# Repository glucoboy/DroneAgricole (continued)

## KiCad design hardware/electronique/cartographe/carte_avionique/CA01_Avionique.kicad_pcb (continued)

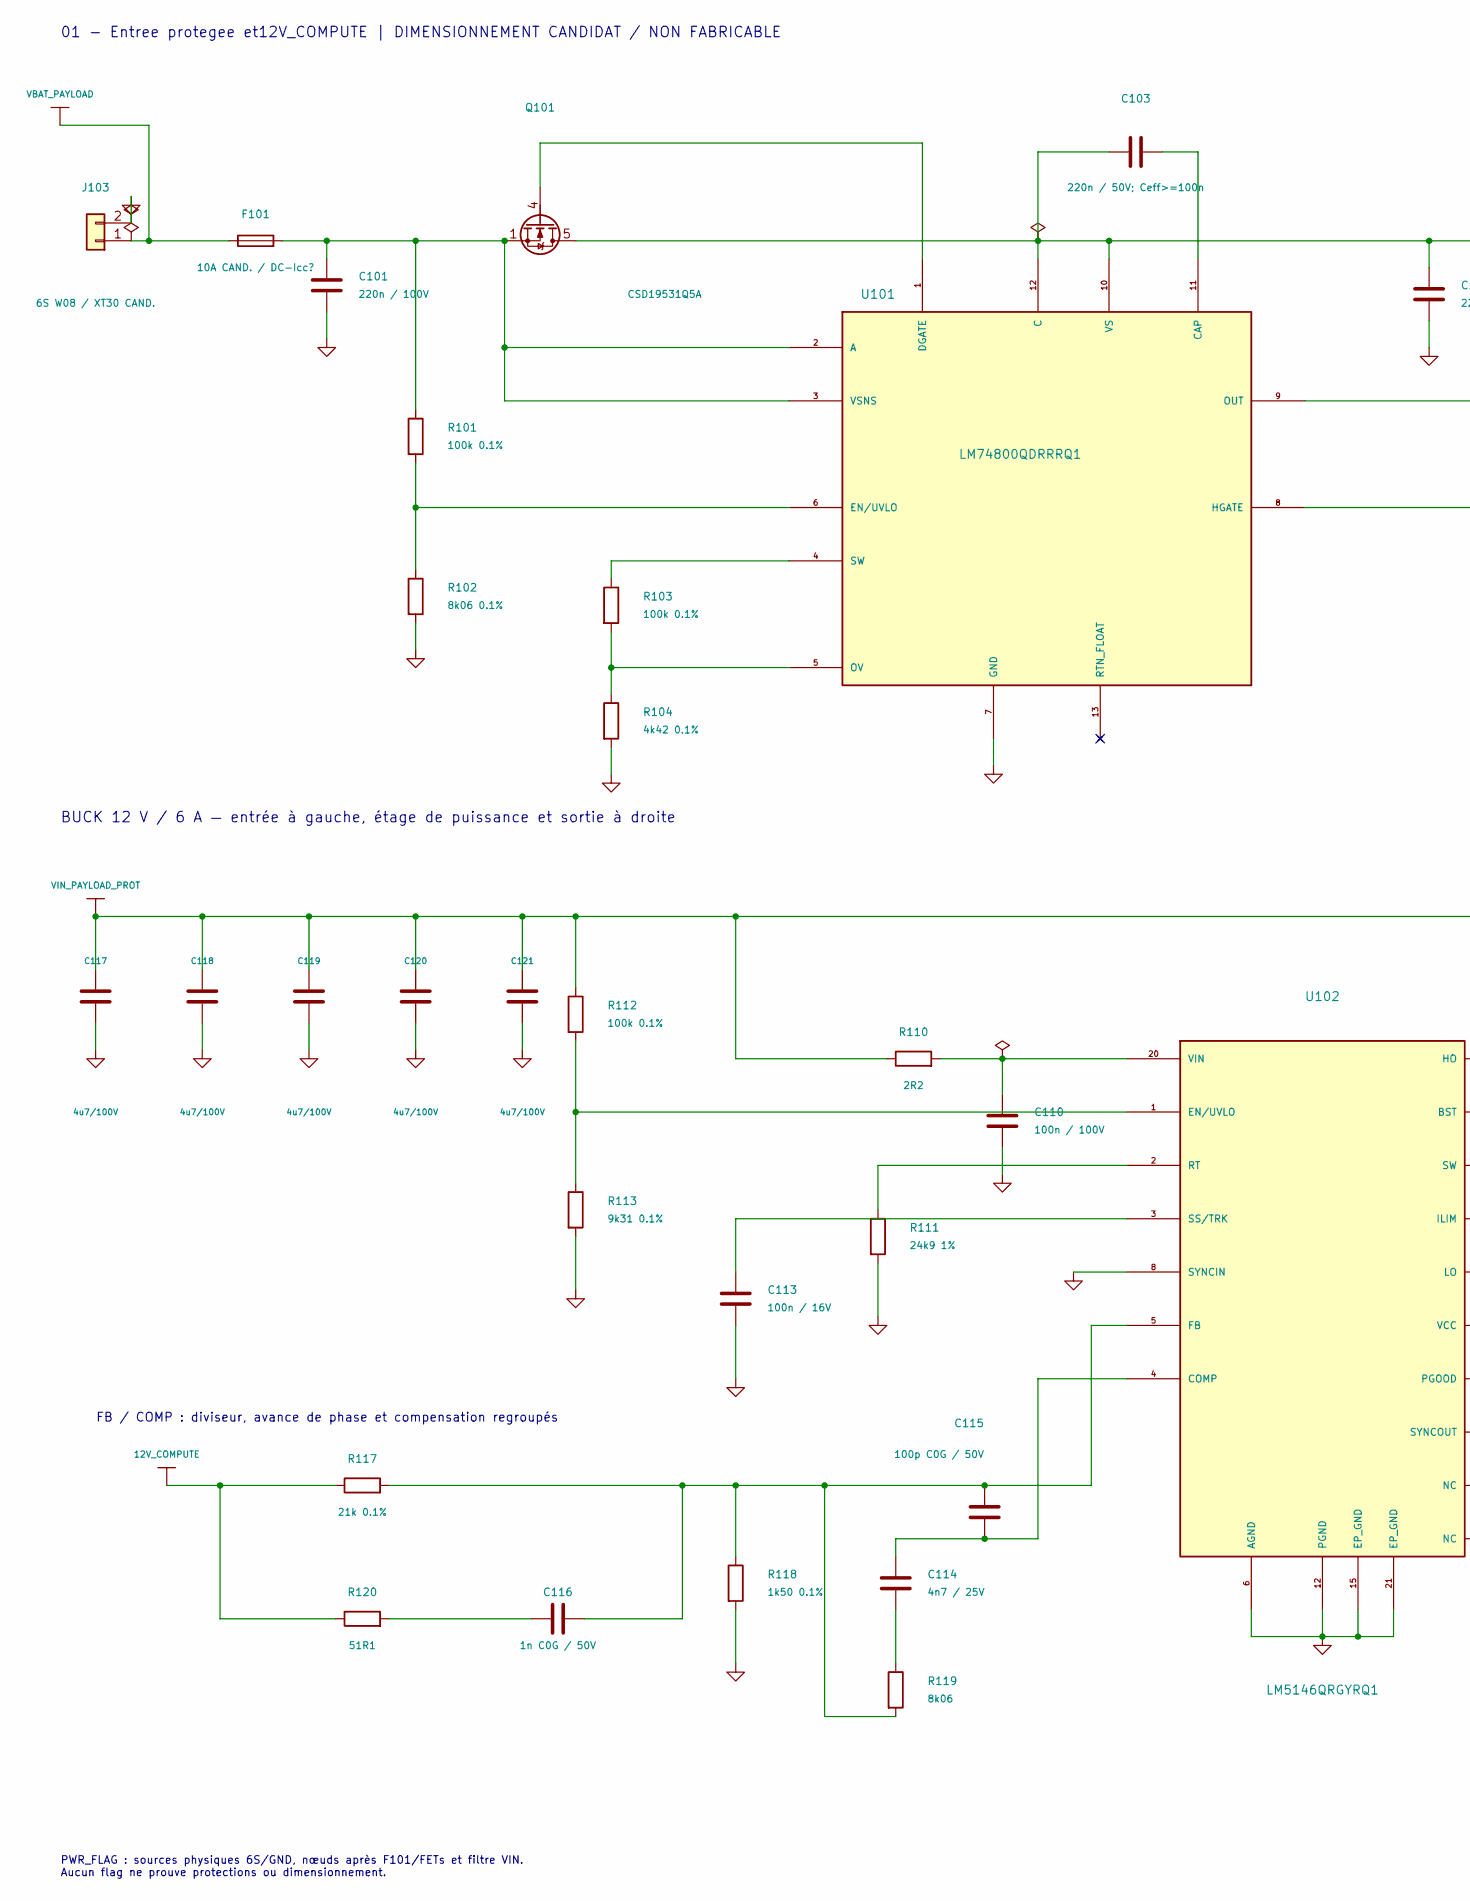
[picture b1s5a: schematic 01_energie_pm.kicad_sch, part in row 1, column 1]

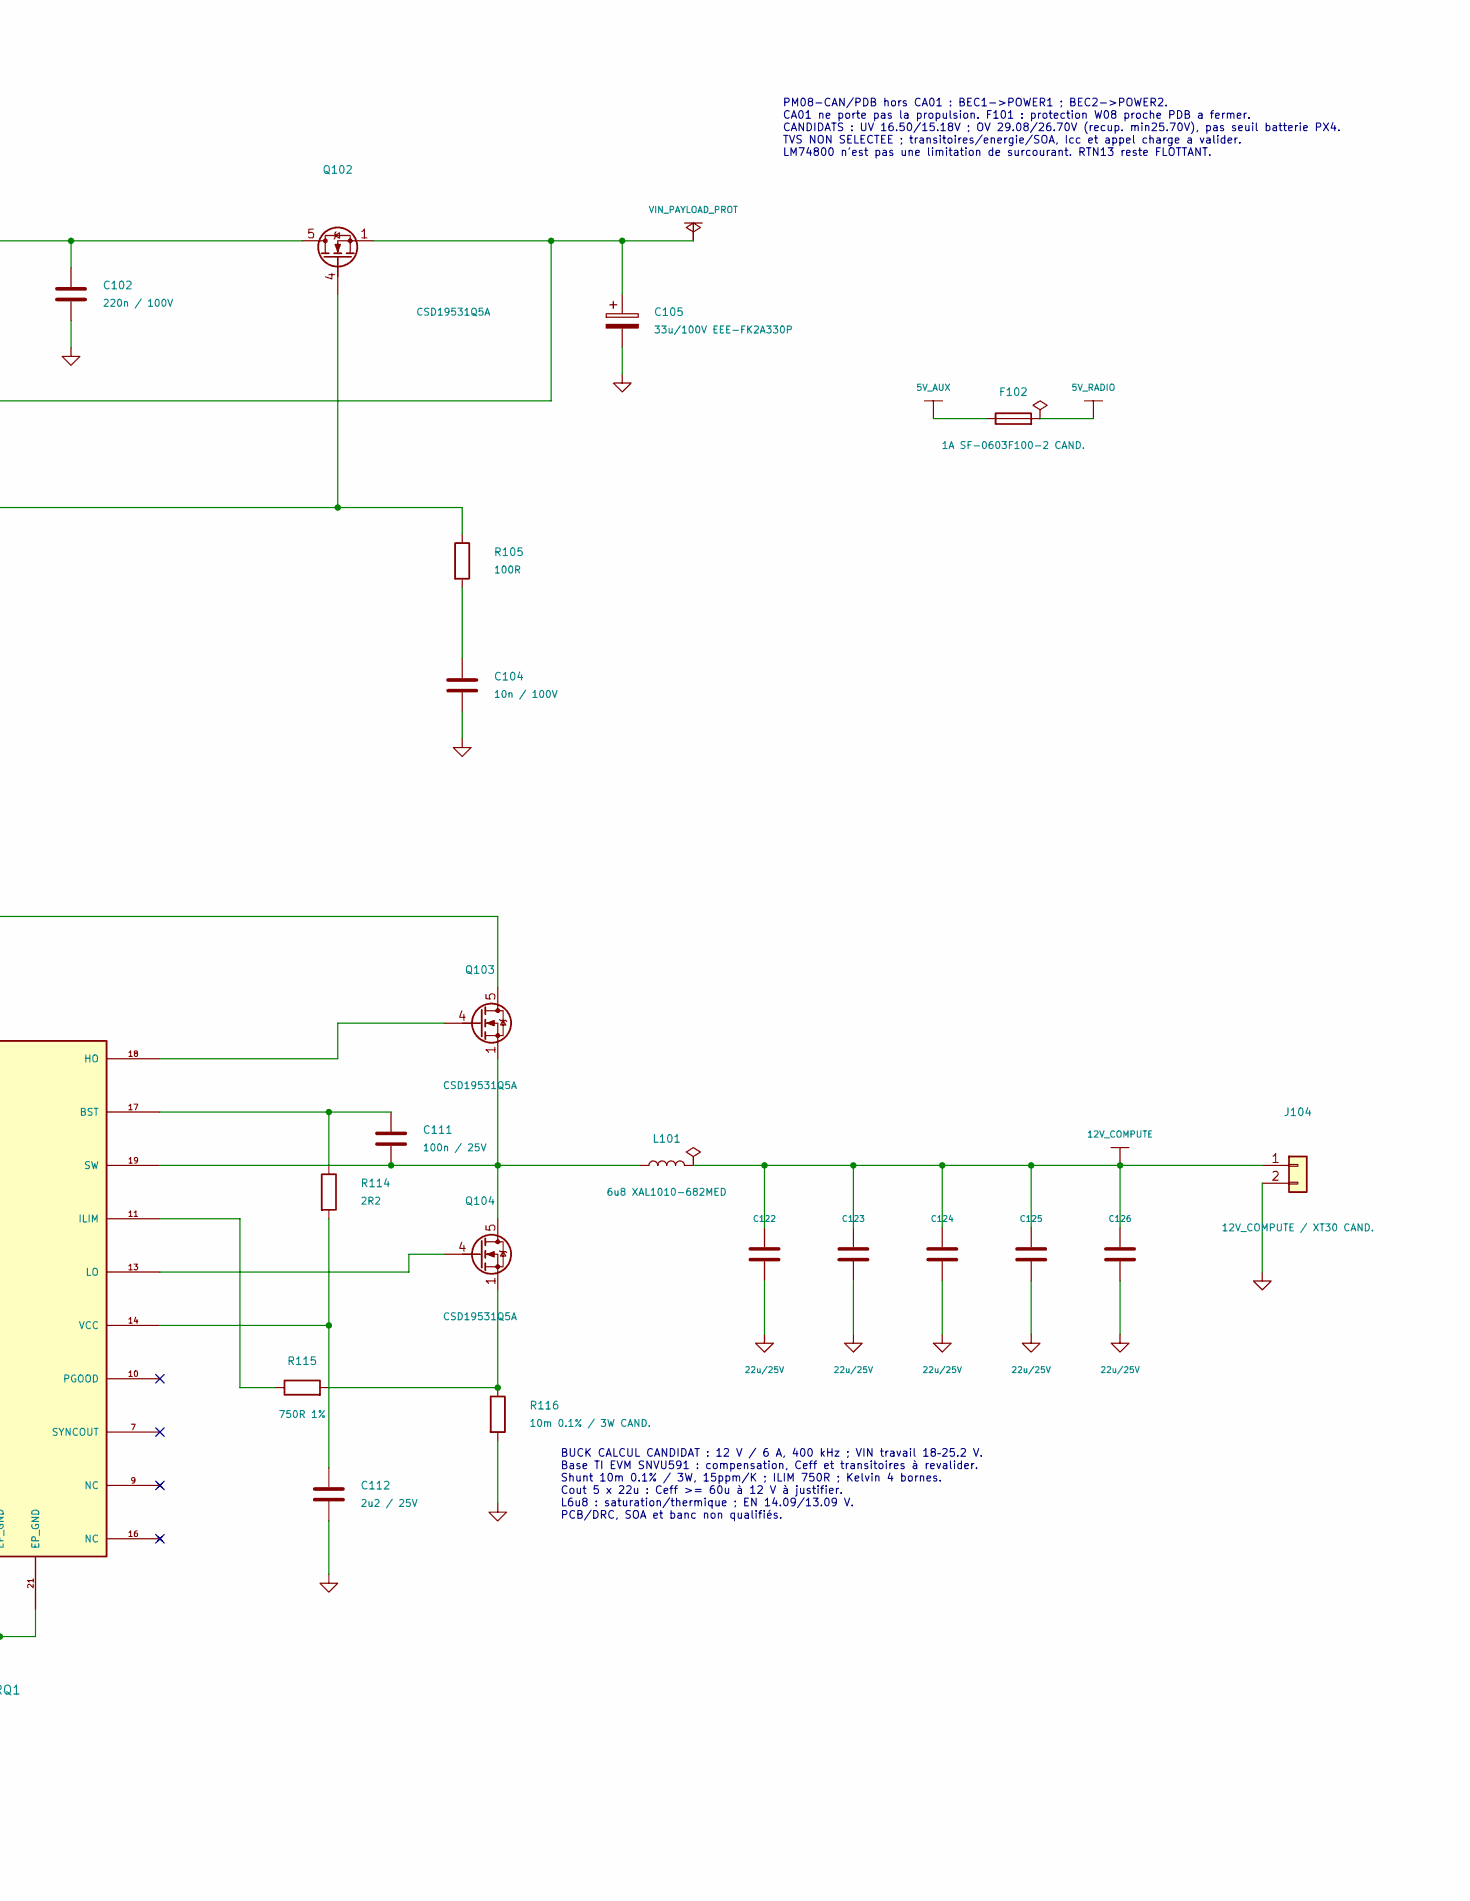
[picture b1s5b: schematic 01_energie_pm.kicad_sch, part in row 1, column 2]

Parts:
C101, C102: 220n / 100V; C_0603_1608Metric
C103: 220n / 50V; Ceff>=100n; C_0603_1608Metric
C104: 10n / 100V; C_0603_1608Metric
C105: 33u/100V EEE-FK2A330P; CP_Elec_8x10.5; MPN EEE-FK2A330P
C110: 100n / 100V; C_0603_1608Metric
C111: 100n / 25V; C_0603_1608Metric
C112: 2u2 / 25V; C_0603_1608Metric
C113: 100n / 16V; C_0603_1608Metric
C114: 4n7 / 25V; C_0603_1608Metric
C115: 100p C0G / 50V; C_0603_1608Metric
C116: 1n C0G / 50V; C_0603_1608Metric
C117, C118, C119, C120, C121: 4u7/100V; C_1210_3225Metric
C122, C123, C124, C125, C126: 22u/25V; C_1210_3225Metric
F101: 10A CAND. / DC-Icc?; Fuse_Littelfuse-NANO2-451_453; MPN 0451010.MRL
F102: 1A SF-0603F100-2 CAND.; Fuse_0603_1608Metric; MPN SF-0603F100-2
J103: 6S W08 / XT30 CAND.; XT30PW_M_CA01_PositivePin1; MPN XT30PW-M30.G.Y
J104: 12V_COMPUTE / XT30 CAND.; XT30PW_F_CA01_PositivePin1; MPN XT30PW-F30.G.Y
L101: 6u8 XAL1010-682MED; L_Coilcraft_XAL1010-XXX; MPN XAL1010-682MED
Q101, Q102, Q103, Q104: CSD19531Q5A; TI_Q5A_CSD19531; MPN CSD19531Q5A
R101, R103, R112: 100k 0.1%; R_0603_1608Metric
R102: 8k06 0.1%; R_0603_1608Metric
R104: 4k42 0.1%; R_0603_1608Metric
R105: 100R; R_0603_1608Metric
R110, R114: 2R2; R_0603_1608Metric
R111: 24k9 1%; R_0603_1608Metric
R113: 9k31 0.1%; R_0603_1608Metric
R115: 750R 1%; R_0603_1608Metric
R116: 10m 0.1% / 3W CAND.; VPG_CSM3637; MPN Y14880R01000B9R
R117: 21k 0.1%; R_0603_1608Metric
R118: 1k50 0.1%; R_0603_1608Metric
R119: 8k06; R_0603_1608Metric
R120: 51R1; R_0603_1608Metric
U101: LM74800QDRRRQ1; WSON-12-1EP_3x3mm_P0.5mm_EP1.5x2.5mm; MPN LM74800QDRRRQ1
U102: LM5146QRGYRQ1; Texas_RGY_R-PVQFN-N20_EP2.05x3.05mm; MPN LM5146QRGYRQ1

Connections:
5V_AUX: F102.1; also elsewhere on the board
5V_RADIO: F102.2; also elsewhere on the board
12V_COMPUTE: C122.1, C123.1, C124.1, C125.1, C126.1, J104.1, L101.2, R117.1, R120.1
GND: C101.2, C102.2, C104.2, C105.2, C110.2, C112.2, C113.2, C117.2, C118.2, C119.2, C120.2, C121.2, C122.2, C123.2, C124.2, C125.2, C126.2, J103.2, J104.2, R102.2, R104.2, R111.2, R113.2, R116.2, R118.2, U101.7 (GND), U102.6 (AGND), U102.8 (SYNCIN), U102.12 (PGND), U102.15 (EP_GND), U102.21 (EP_GND); also elsewhere on the board
unnamed: C104.1, R105.2
unnamed: C114.2, R119.1
unnamed: C116.1, R120.2
unnamed: C102.1, C103.2, Q101.5 (D), Q102.5 (D), U101.10 (VS), U101.12 (C)
unnamed: Q101.4 (G), U101.1 (DGATE)
unnamed: Q102.4 (G), R105.1, U101.8 (HGATE)
unnamed: Q103.4 (G), U102.18 (HO)
unnamed: C111.2, L101.1, Q103.1 (S), Q103.2 (S), Q103.3 (S), Q104.5 (D), U102.19 (SW)
unnamed: Q104.4 (G), U102.13 (LO)
unnamed: Q104.1 (S), Q104.2 (S), Q104.3 (S), R115.2, R116.1
unnamed: C101.1, F101.2, Q101.1 (S), Q101.2 (S), Q101.3 (S), R101.1, U101.2 (A), U101.3 (VSNS)
unnamed: C103.1, U101.11 (CAP)
unnamed: R101.2, R102.1, U101.6 (EN/UVLO)
unnamed: R103.2, R104.1, U101.5 (OV)
unnamed: R103.1, U101.4 (SW)
unnamed: C111.1, R114.1, U102.17 (BST)
unnamed: C114.1, C115.1, U102.4 (COMP)
unnamed: R112.2, R113.1, U102.1 (EN/UVLO)
unnamed: C115.2, C116.2, R117.2, R118.1, R119.2, U102.5 (FB)
unnamed: R115.1, U102.11 (ILIM)
unnamed: R111.1, U102.2 (RT)
unnamed: C113.1, U102.3 (SS/TRK)
unnamed: C112.1, R114.2, U102.14 (VCC)
unnamed: C110.1, R110.2, U102.20 (VIN)
VBAT_PAYLOAD: F101.1, J103.1
VIN_PAYLOAD_PROT: C105.1, C117.1, C118.1, C119.1, C120.1, C121.1, Q102.1 (S), Q102.2 (S), Q102.3 (S), Q103.5 (D), R110.1, R112.1, U101.9 (OUT); also elsewhere on the board

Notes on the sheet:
PM08-CAN/PDB hors CA01 : BEC1->POWER1 ; BEC2->POWER2. CA01 ne porte pas la propulsion. F101 : protection W08 proche PDB a fermer. CANDIDATS : UV 16.50/15.18V ; OV 29.08/26.70V (recup. min25.70V), pas seuil batterie PX4. TVS NON SELECTEE ; transitoires/energie/SOA, Icc et appel charge a valider. LM7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
01 - Entree protegee et12V_COMPUTE | DIMENSIONNEMENT CANDIDAT / NON FABRICABLE
BUCK 12 V / 6 A — entrée à gauche, étage de puissance et sortie à droite
FB / COMP : diviseur, avance de phase et compensation regroupés
PWR_FLAG : sources physiques 6S/GND, nœuds après F101/FETs et filtre VIN. Aucun flag ne prouve protections ou dimensionnement.
BUCK CALCUL CANDIDAT : 12 V / 6 A, 400 kHz ; VIN travail 18–25.2 V. Base TI EVM SNVU591 : compensation, Ceff et transitoires à revalider. Shunt 10m 0.1% / 3W, 15ppm/K ; ILIM 750R ; Kelvin 4 bornes. Cout 5 x 22u : Ceff >= 60u à 12 V à justifier. L6u8 : saturation/thermique ; EN 14.09/13.09 V. PCB/DR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

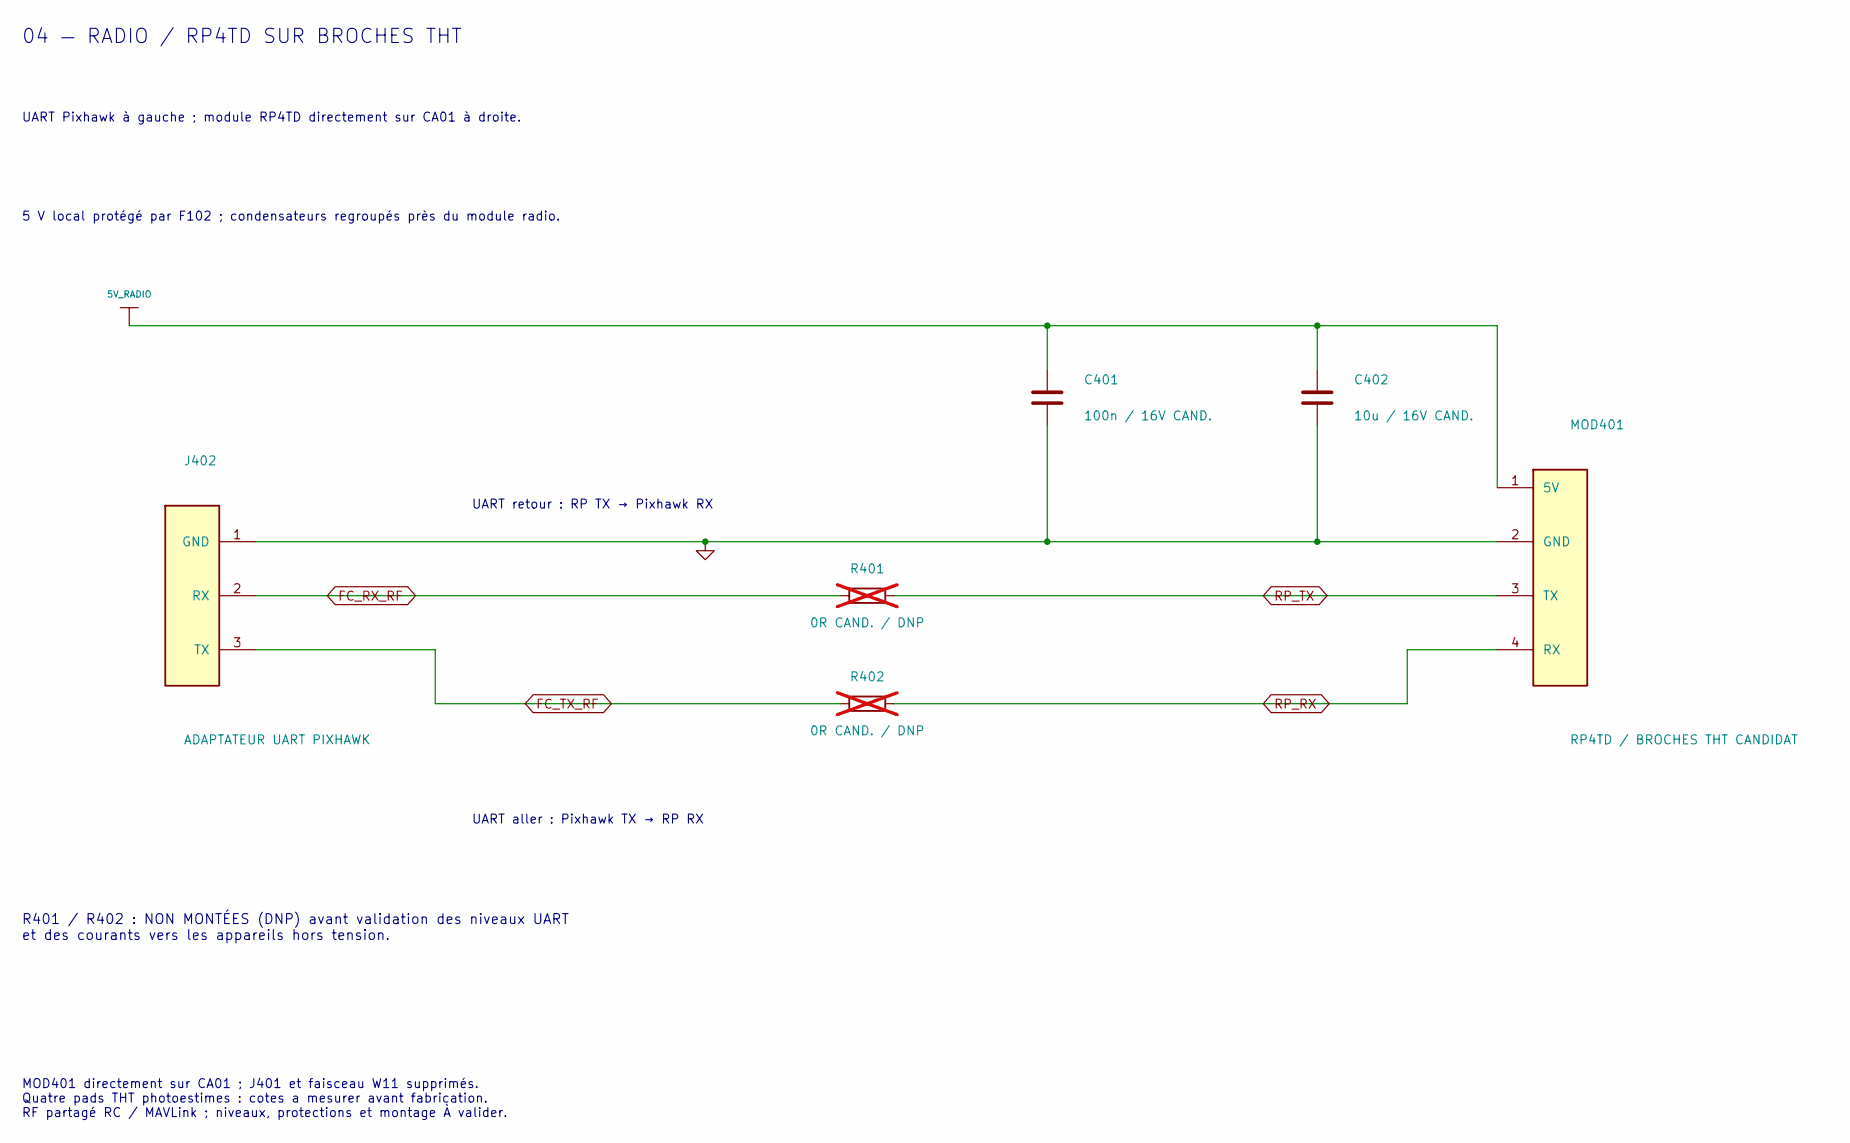
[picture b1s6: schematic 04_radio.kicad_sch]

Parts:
C401: 100n / 16V CAND.; C_0603_1608Metric; MPN C1608X7R1H104K080AA
C402: 10u / 16V CAND.; C_0805_2012Metric; MPN CGA4J1X5R1C106K125AC
J402: ADAPTATEUR UART PIXHAWK; JST_GH_SM03B-GHS-TB_1x03-1MP_P1.25mm_Horizontal; MPN SM03B-GHS-TB(LF)(SN)
MOD401: RP4TD / BROCHES THT CANDIDAT; RadioMaster_RP4TD_Broches_THT_Candidat; MPN HP0157.RX-RP4TD-LBT
R401, R402: 0R CAND. / DNP; R_0603_1608Metric; MPN CRCW06030000Z0EA; not fitted

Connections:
5V_RADIO: C401.1, C402.1, MOD401.1 (5V); also elsewhere on the board
FC_RX_RF: J402.2 (RX), R401.2
FC_TX_RF: J402.3 (TX), R402.1
GND: C401.2, C402.2, J402.1 (GND), MOD401.2 (GND); also elsewhere on the board
RP_RX: MOD401.4 (RX), R402.2
RP_TX: MOD401.3 (TX), R401.1

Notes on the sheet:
04 — RADIO / RP4TD SUR BROCHES THT
UART Pixhawk à gauche ; module RP4TD directement sur CA01 à droite.
5 V local protégé par F102 ; condensateurs regroupés près du module radio.
UART retour : RP TX → Pixhawk RX
UART aller : Pixhawk TX → RP RX
R401 / R402 : NON MONTÉES (DNP) avant validation des niveaux UART et des courants vers les appareils hors tension.
MOD401 directement sur CA01 ; J401 et faisceau W11 supprimés. Quatre pads THT photoestimes : cotes a mesurer avant fabrication. RF partagé RC / MAVLink ; niveaux, protections et montage À valider.

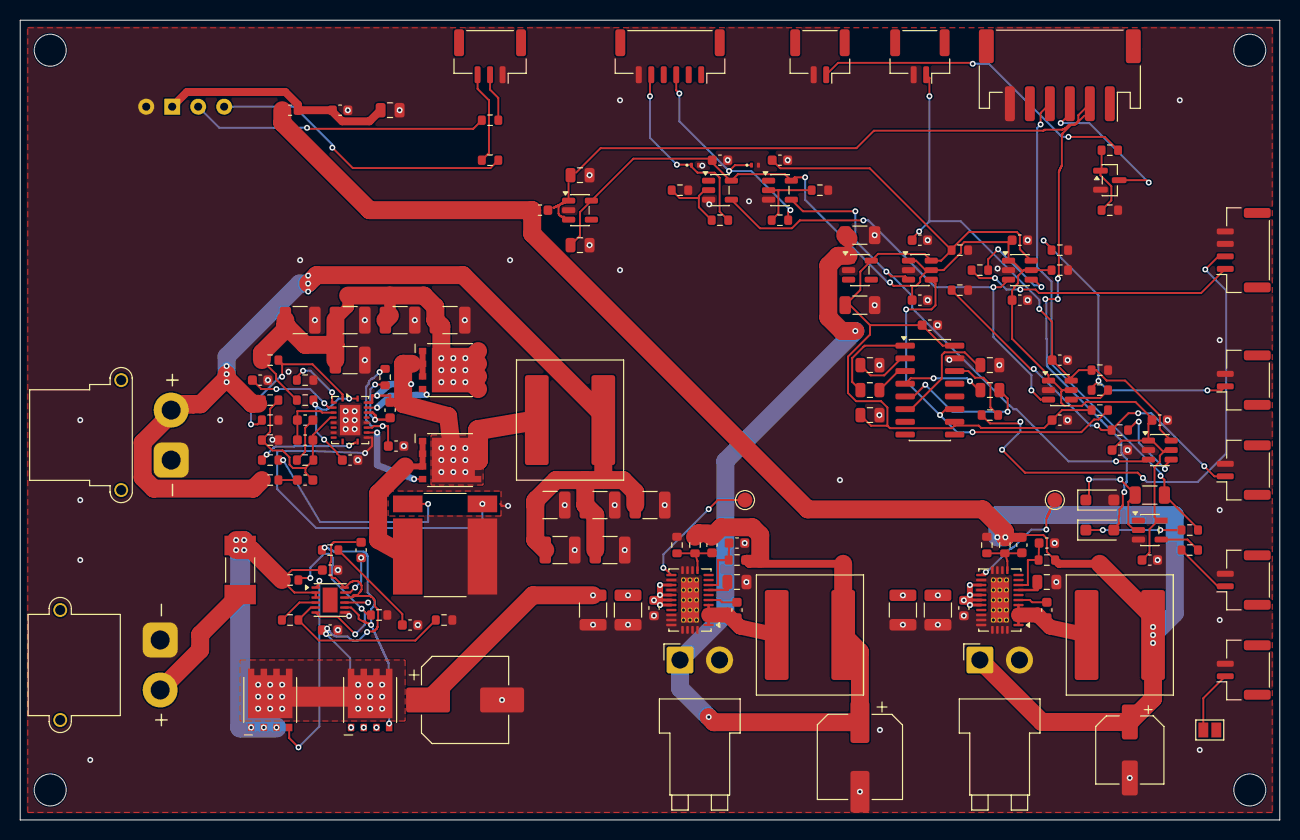
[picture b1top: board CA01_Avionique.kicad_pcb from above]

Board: 4 copper layers, 126.0 x 80.0 mm, 155 parts (0 on the bottom side), 81 nets.

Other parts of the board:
H1, H2, H3, H4: Fixation M3 / Holybro; MountingHole_3.2mm_M3

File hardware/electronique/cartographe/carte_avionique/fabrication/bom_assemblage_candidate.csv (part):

"reference","quantite_candidate","valeur_bom","valeur_pcb","mpn_bom","mpn_netlist","fabricant_netlist","empreinte_bom","empreinte_pcb","type_assemblage","face_pcb","dnp_bom","dnp_schema","dnp_pcb","exclu_fabrication_bom","exclu_bom_pcb","exclu_placement_pcb","statut_montage","statut_conception_bom","qualification","montage_physique_execute","ecarts_sources","limites","datasheet_bom","datasheet_schema"
"C101","1","220n / 100V","220n / 100V","","","","Capacitor_SMD:C_0603_1608Metric","Capacitor_SMD:C_0603_1608Metric","SMD","F.Cu","false","false","false","false","false","false","À monter après clôture","À valider","À valider","false","","Référence commandable à sélectionner ; valeur candidate seulement","",""
"C102","1","220n / 100V","220n / 100V","","","","Capacitor_SMD:C_0603_1608Metric","Capacitor_SMD:C_0603_1608Metric","SMD","F.Cu","false","false","false","false","false","false","À monter après clôture","À valider","À valider","false","","Référence commandable à sélectionner ; valeur candidate seulement","",""
"C103","1","220n / 50V; Ceff>=100n","220n / 50V; Ceff>=100n","","","","Capacitor_SMD:C_0603_1608Metric","Capacitor_SMD:C_0603_1608Metric","SMD","F.Cu","false","false","false","false","false","false","À monter après clôture","À valider","À valider","false","","Référence commandable à sélectionner ; valeur candidate seulement","",""
"C104","1","10n / 100V","10n / 100V","","","","Capacitor_SMD:C_0603_1608Metric","Capacitor_SMD:C_0603_1608Metric","SMD","F.Cu","false","false","false","false","false","false","À monter après clôture","À valider","À valider","false","","Référence commandable à sélectionner ; valeur candidate seulement","",""
"C105","1","33u/100V EEE-FK2A330P","33u/100V EEE-FK2A330P","EEE-FK2A330P","EEE-FK2A330P","","Capacitor_SMD:CP_Elec_8x10.5","Capacitor_SMD:CP_Elec_8x10.5","SMD","F.Cu","false","false","false","false","false","false","À monter après clôture","À valider","À valider","false","","","",""
"C110","1","100n / 100V","100n / 100V","","","","Capacitor_SMD:C_0603_1608Metric","Capacitor_SMD:C_0603_1608Metric","SMD","F.Cu","false","false","false","false","false","false","À monter après clôture","À valider","À valider","false","","Référence commandable à sélectionner ; valeur candidate seulement","",""
"C111","1","100n / 25V","100n / 25V","","","","Capacitor_SMD:C_0603_1608Metric","Capacitor_SMD:C_0603_1608Metric","SMD","F.Cu","false","false","false","false","false","false","À monter après clôture","À valider","À valider","false","","Référence commandable à sélectionner ; valeur candidate seulement","",""
"C112","1","2u2 / 25V","2u2 / 25V","","","","Capacitor_SMD:C_0603_1608Metric","Capacitor_SMD:C_0603_1608Metric","SMD","F.Cu","false","false","false","false","false","false","À monter après clôture","À valider","À valider","false","","Référence commandable à sélectionner ; valeur candidate seulement","",""
"C113","1","100n / 16V","100n / 16V","","","","Capacitor_SMD:C_0603_1608Metric","Capacitor_SMD:C_0603_1608Metric","SMD","F.Cu","false","false","false","false","false","false","À monter après clôture","À valider","À valider","false","","Référence commandable à sélectionner ; valeur candidate seulement","",""
"C114","1","4n7 / 25V","4n7 / 25V","","","","Capacitor_SMD:C_0603_1608Metric","Capacitor_SMD:C_0603_1608Metric","SMD","F.Cu","false","false","false","false","false","false","À monter après clôture","À valider","À valider","false","","Référence commandable à sélectionner ; valeur candidate seulement","",""
"C115","1","100p C0G / 50V","100p C0G / 50V","","","","Capacitor_SMD:C_0603_1608Metric","Capacitor_SMD:C_0603_1608Metric","SMD","F.Cu","false","false","false","false","false","false","À monter après clôture","À valider","À valider","false","","Référence commandable à sélectionner ; valeur candidate seulement","",""
"C116","1","1n C0G / 50V","1n C0G / 50V","","","","Capacitor_SMD:C_0603_1608Metric","Capacitor_SMD:C_0603_1608Metric","SMD","F.Cu","false","false","false","false","false","false","À monter après clôture","À valider","À valider","false","","Référence commandable à sélectionner ; valeur candidate seulement","",""
"C117","1","4u7/100V","4u7/100V","","","","Capacitor_SMD:C_1210_3225Metric","Capacitor_SMD:C_1210_3225Metric","SMD","F.Cu","false","false","false","false","false","false","À monter après clôture","À valider","À valider","false","","Référence commandable à sélectionner ; valeur candidate seulement","",""
"C118","1","4u7/100V","4u7/100V","","","","Capacitor_SMD:C_1210_3225Metric","Capacitor_SMD:C_1210_3225Metric","SMD","F.Cu","false","false","false","false","false","false","À monter après clôture","À valider","À valider","false","","Référence commandable à sélectionner ; valeur candidate seulement","",""
"C119","1","4u7/100V","4u7/100V","","","","Capacitor_SMD:C_1210_3225Metric","Capacitor_SMD:C_1210_3225Metric","SMD","F.Cu","false","false","false","false","false","false","À monter après clôture","À valider","À valider","false","","Référence commandable à sélectionner ; valeur candidate seulement","",""
"C120","1","4u7/100V","4u7/100V","","","","Capacitor_SMD:C_1210_3225Metric","Capacitor_SMD:C_1210_3225Metric","SMD","F.Cu","false","false","false","false","false","false","À monter après clôture","À valider","À valider","false","","Référence commandable à sélectionner ; valeur candidate seulement","",""
"C121","1","4u7/100V","4u7/100V","","","","Capacitor_SMD:C_1210_3225Metric","Capacitor_SMD:C_1210_3225Metric","SMD","F.Cu","false","false","false","false","false","false","À monter après clôture","À valider","À valider","false","","Référence commandable à sélectionner ; valeur candidate seulement","",""
"C122","1","22u/25V","22u/25V","","","","Capacitor_SMD:C_1210_3225Metric","Capacitor_SMD:C_1210_3225Metric","SMD","F.Cu","false","false","false","false","false","false","À monter après clôture","À valider","À valider","false","","Référence commandable à sélectionner ; valeur candidate seulement","",""
"C123","1","22u/25V","22u/25V","","","","Capacitor_SMD:C_1210_3225Metric","Capacitor_SMD:C_1210_3225Metric","SMD","F.Cu","false","false","false","false","false","false","À monter après clôture","À valider","À valider","false","","Référence commandable à sélectionner ; valeur candidate seulement","",""
"C124","1","22u/25V","22u/25V","","","","Capacitor_SMD:C_1210_3225Metric","Capacitor_SMD:C_1210_3225Metric","SMD","F.Cu","false","false","false","false","false","false","À monter après clôture","À valider","À valider","false","","Référence commandable à sélectionner ; valeur candidate seulement","",""
"C125","1","22u/25V","22u/25V","","","","Capacitor_SMD:C_1210_3225Metric","Capacitor_SMD:C_1210_3225Metric","SMD","F.Cu","false","false","false","false","false","false","À monter après clôture","À valider","À valider","false","","Référence commandable à sélectionner ; valeur candidate seulement","",""
"C126","1","22u/25V","22u/25V","","","","Capacitor_SMD:C_1210_3225Metric","Capacitor_SMD:C_1210_3225Metric","SMD","F.Cu","false","false","false","false","false","false","À monter après clôture","À valider","À valider","false","","Référence commandable à sélectionner ; valeur candidate seulement","",""
"C201","1","10u / 50V X7R","10u / 50V X7R","C3225X7R1H106K250AC","C3225X7R1H106K250AC","TDK","Capacitor_SMD:C_1210_3225Metric","Capacitor_SMD:C_1210_3225Metric","SMD","F.Cu","false","false","false","false","false","false","À monter après clôture","À valider","À valider","false","","","https://product.tdk.com/en/search/capacitor/ceramic/mlcc/inf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","https://product.tdk.com/en/search/capacitor/ceramic/mlcc/inf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"
"C202","1","470n / 25V X7R","470n / 25V X7R","C1608X7R1E474K080AB","C1608X7R1E474K080AB","TDK","Capacitor_SMD:C_0603_1608Metric","Capacitor_SMD:C_0603_1608Metric","SMD","F.Cu","false","false","false","false","false","false","À monter après clôture","À valider","À valider","false","","","https://product.tdk.com/en/search/capacitor/ceramic/mlcc/inf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","https://product.tdk.com/en/search/capacitor/ceramic/mlcc/inf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"
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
